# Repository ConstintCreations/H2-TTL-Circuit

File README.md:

# Eight PCB

This is an astable multivibrator that I made for Week 2 of [Hack Club](https://hackclub.com/)'s [Resolution Program](https://resolution.hackclub.com/)'s Hardware Pathway.

## Simulation

This is an astable multivibrator which uses 2 transistors that take turns turning each other off with capacitors creating a delay. This creates oscilation which makes an LED blink. When the left switch is down, the LED will turn off, and when the right switch is down, the LED will blink. If the right switch is up, the LED will not blink, but will stay on.

[Link to Demo](https://is.gd/ewByXw)

## Schematic

## PCB

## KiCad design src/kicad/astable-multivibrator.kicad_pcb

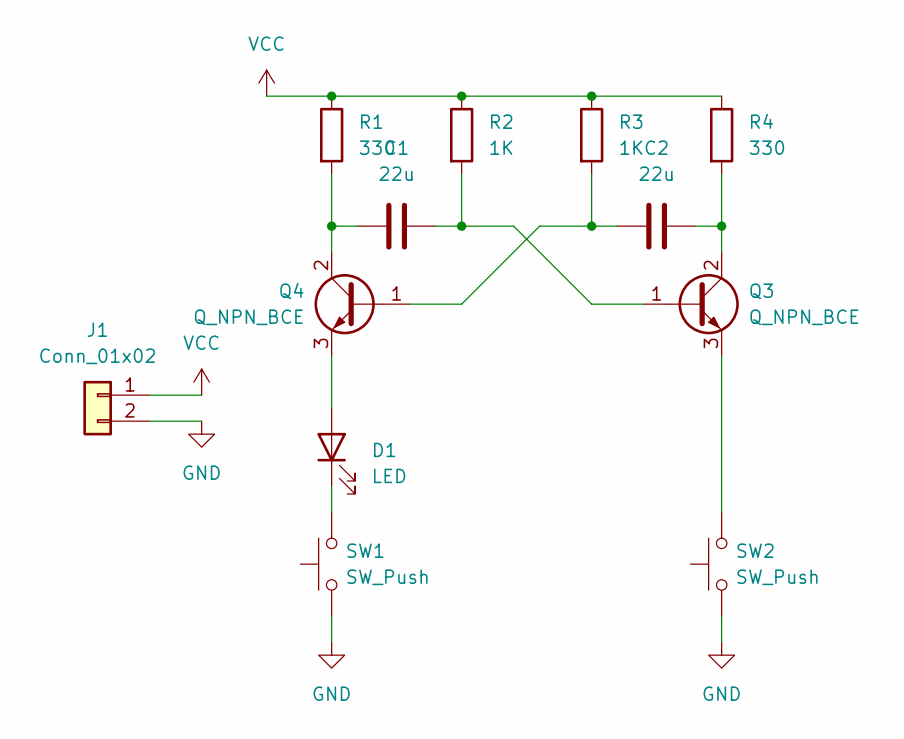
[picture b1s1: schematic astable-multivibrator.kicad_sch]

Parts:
C1, C2: 22u; C_Disc_D5.0mm_W2.5mm_P5.00mm
D1: LED; LED_D5.0mm
J1: Conn_01x02; PinHeader_1x02_P2.54mm_Vertical
Q3, Q4: Q_NPN_BCE; TO-92L_Inline_Wide
R1, R4: 330; R_Axial_DIN0204_L3.6mm_D1.6mm_P7.62mm_Horizontal
R2, R3: 1K; R_Axial_DIN0204_L3.6mm_D1.6mm_P7.62mm_Horizontal
SW1, SW2: SW_Push; SW_PUSH_6mm

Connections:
GND: J1.2, SW1.1, SW2.1
unnamed: D1.2 (A), Q4.3 (E)
unnamed: D1.1 (K), SW1.2
unnamed: C1.2, Q3.1 (B), R2.2
unnamed: C2.2, Q3.2 (C), R4.2
unnamed: Q3.3 (E), SW2.2
unnamed: C2.1, Q4.1 (B), R3.2
unnamed: C1.1, Q4.2 (C), R1.2
VCC: J1.1, R1.1, R2.1, R3.1, R4.1

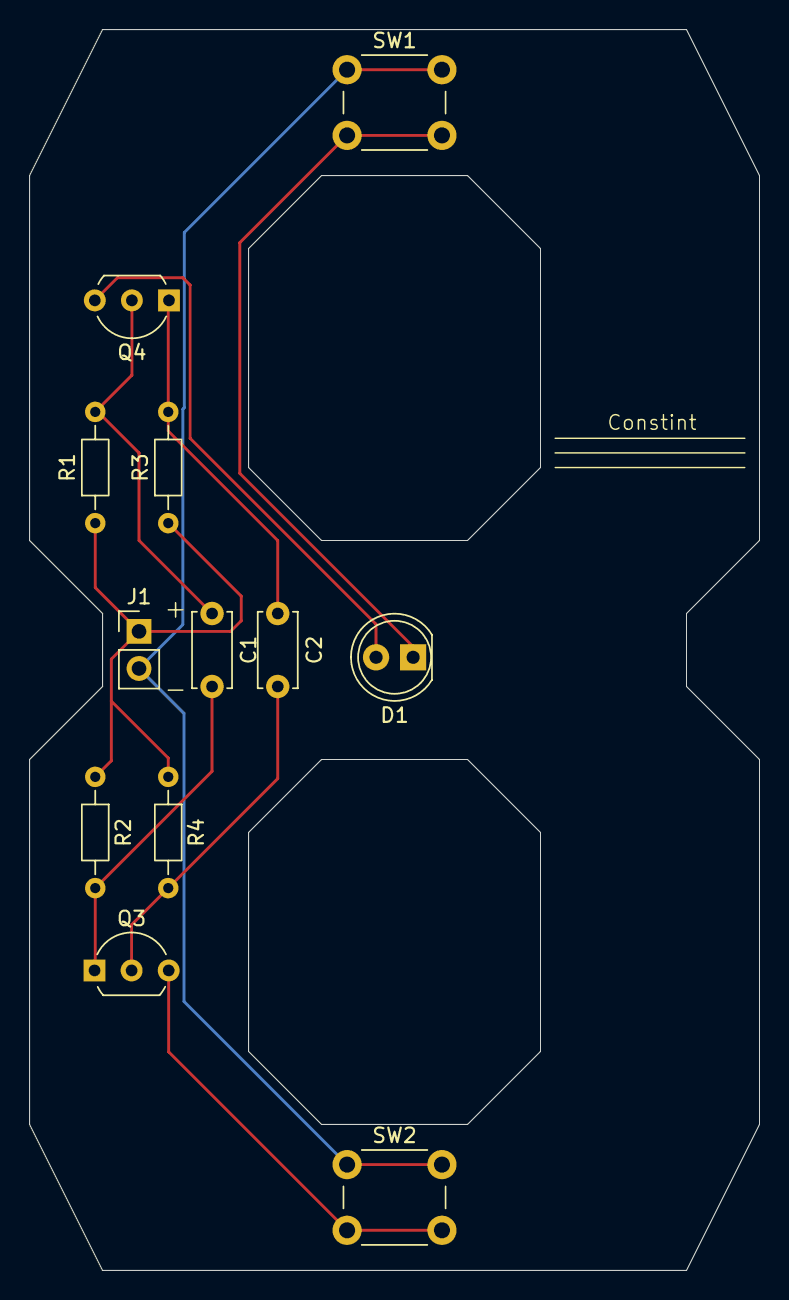
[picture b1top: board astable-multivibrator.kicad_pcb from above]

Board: 2 copper layers, 50.0 x 85.0 mm, 12 parts (0 on the bottom side), 9 nets.

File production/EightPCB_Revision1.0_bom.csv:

Designator,Footprint,Quantity,Value,LCSC Part #
"C1, C2",C_Disc_D5.0mm_W2.5mm_P5.00mm,2,22u,
D1,LED_D5.0mm,1,LED,
J1,PinHeader_1x02_P2.54mm_Vertical,1,Conn_01x02,
"Q3, Q4",TO-92L_Inline_Wide,2,Q_NPN_BCE,
"R1, R4",R_Axial_DIN0204_L3.6mm_D1.6mm_P7.62mm_Horizontal,2,330,
"R2, R3",R_Axial_DIN0204_L3.6mm_D1.6mm_P7.62mm_Horizontal,2,1K,
"SW1, SW2",SW_PUSH_6mm,2,SW_Push,

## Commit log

2026-03-22 Added Project Files, Images, and README
